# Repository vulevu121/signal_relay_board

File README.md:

# Signal Relay Board Layout
This board aims to relay signals for the battery management system in an electric FSAE vehicle.

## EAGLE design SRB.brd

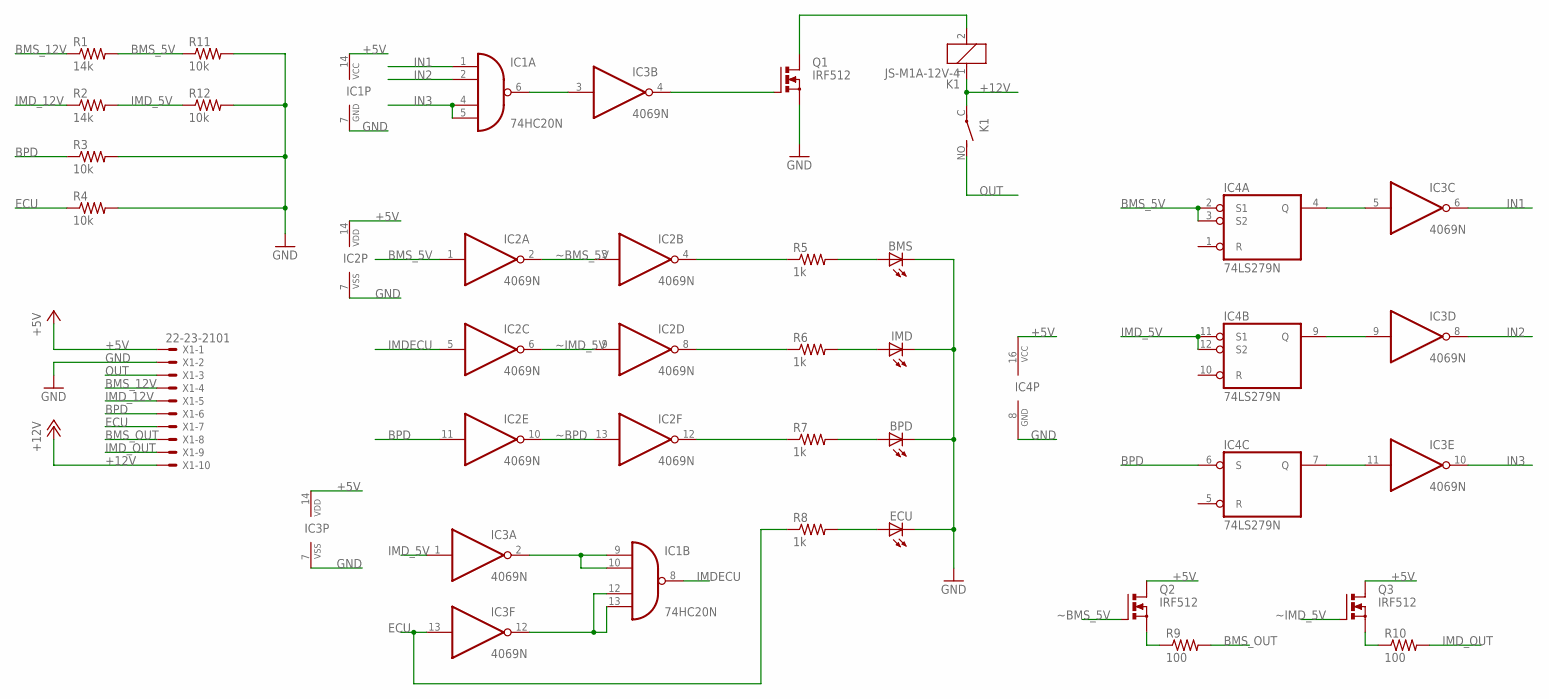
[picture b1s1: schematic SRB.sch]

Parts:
BMS: LED5MM
BPD: LED5MM
ECU: LED5MM
IC1: 74HC20N; DIL14
IC2, IC3: 4069N; DIL14
IC4: 74LS279N; DIL16
IMD: LED5MM
K1: JS-M1A-12V-4; JS-M1A
Q1, Q2, Q3: IRF512; TO220BV
R1, R2: 14k; 0207/10
R3, R4, R11, R12: 10k; 0207/10
R5, R6, R7, R8: 1k; 0207/10
R9, R10: 100; 0207/10
X1: 22-23-2101

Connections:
+5V: IC1.14 (VCC), IC2.14 (VDD), IC3.14 (VDD), IC4.16 (VCC), Q2.D, Q3.D, X1.1
+12V: K1.1, K1.C, X1.10
BMS_5V: IC2.1 (I), IC4.2 (S1), IC4.3 (S2), R1.2, R11.1
BMS_12V: R1.1, X1.4
BMS_OUT: R9.2, X1.8
BPD: IC2.11 (I), IC4.6 (S), R3.1, X1.6
ECU: IC3.13 (I), R4.1, R8.1, X1.7
GND: BMS.K (C), BPD.K (C), ECU.K (C), IC1.7 (GND), IC2.7 (VSS), IC3.7 (VSS), IC4.8 (GND), IMD.K (C), Q1.S, R3.2, R4.2, R11.2, R12.2, X1.2
IMDECU: IC1.8 (O), IC2.5 (I)
IMD_5V: IC3.1 (I), IC4.11 (S1), IC4.12 (S2), R2.2, R12.1
IMD_12V: R2.1, X1.5
IMD_OUT: R10.2, X1.9
IN1: IC1.1 (I0), IC3.6 (O)
IN2: IC1.2 (I1), IC3.8 (O)
IN3: IC1.4 (I2), IC1.5 (I3), IC3.10 (O)
unnamed: IC1.6 (O), IC3.3 (I)
unnamed: IC3.4 (O), Q1.G
unnamed: Q2.S, R9.1
unnamed: IC2.4 (O), R5.1
unnamed: IC2.8 (O), R6.1
unnamed: IC2.12 (O), R7.1
unnamed: IC1.12 (I2), IC1.13 (I3), IC3.12 (O)
unnamed: IC1.9 (I0), IC1.10 (I1), IC3.2 (O)
unnamed: BMS.A, R5.2
unnamed: IMD.A, R6.2
unnamed: BPD.A, R7.2
unnamed: ECU.A, R8.2
unnamed: Q3.S, R10.1
unnamed: K1.2, Q1.D
unnamed: IC3.5 (I), IC4.4 (Q)
unnamed: IC3.9 (I), IC4.9 (Q)
unnamed: IC3.11 (I), IC4.7 (Q)
OUT: K1.NO (S), X1.3
~BMS_5V: IC2.2 (O), IC2.3 (I), Q2.G
~BPD: IC2.10 (O), IC2.13 (I)
~IMD_5V: IC2.6 (O), IC2.9 (I), Q3.G

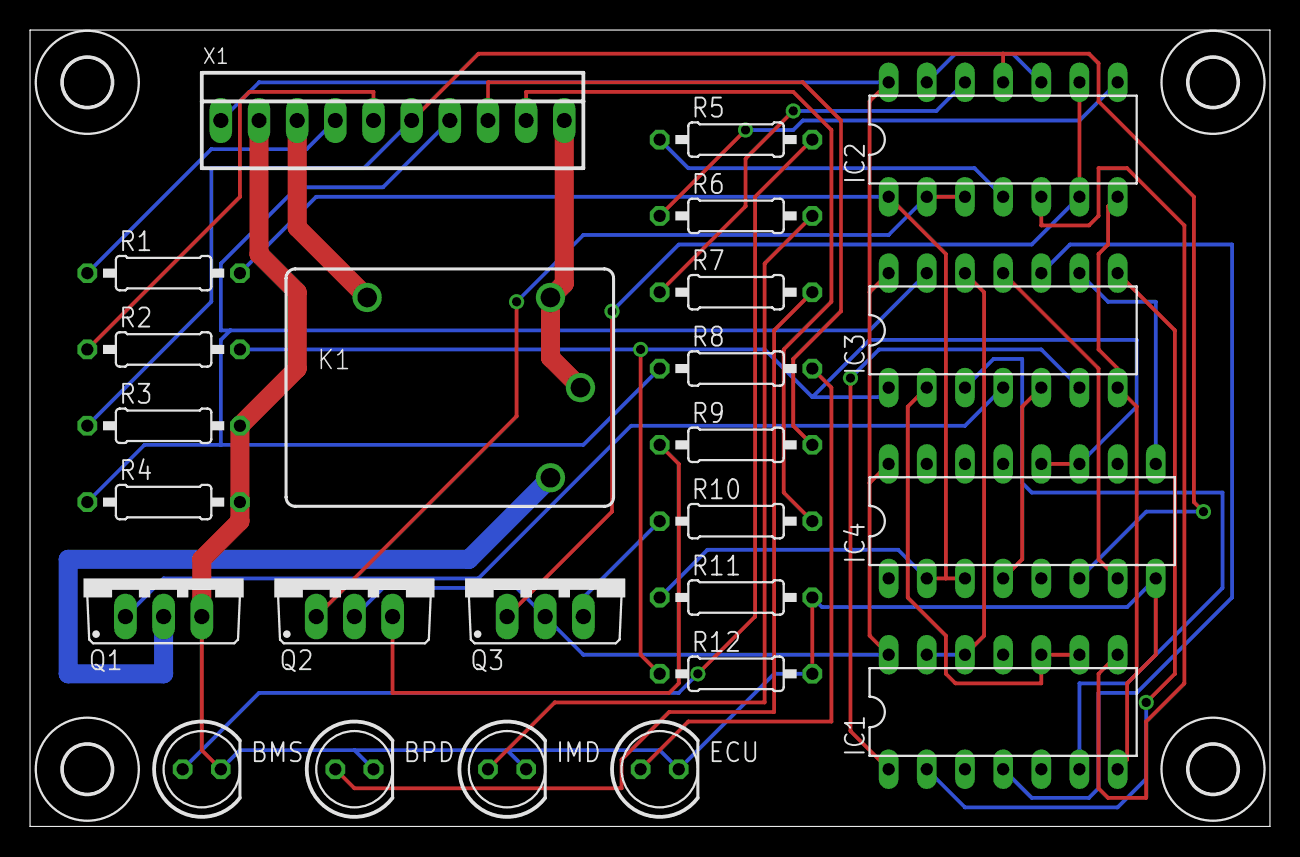
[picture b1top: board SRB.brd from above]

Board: 2 copper layers, 82.5 x 53.0 mm, 29 parts (0 on the bottom side), 36 nets.

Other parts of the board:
U$1, U$2, U$3, U$4: 3,2

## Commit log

2018-05-15 initial upload
